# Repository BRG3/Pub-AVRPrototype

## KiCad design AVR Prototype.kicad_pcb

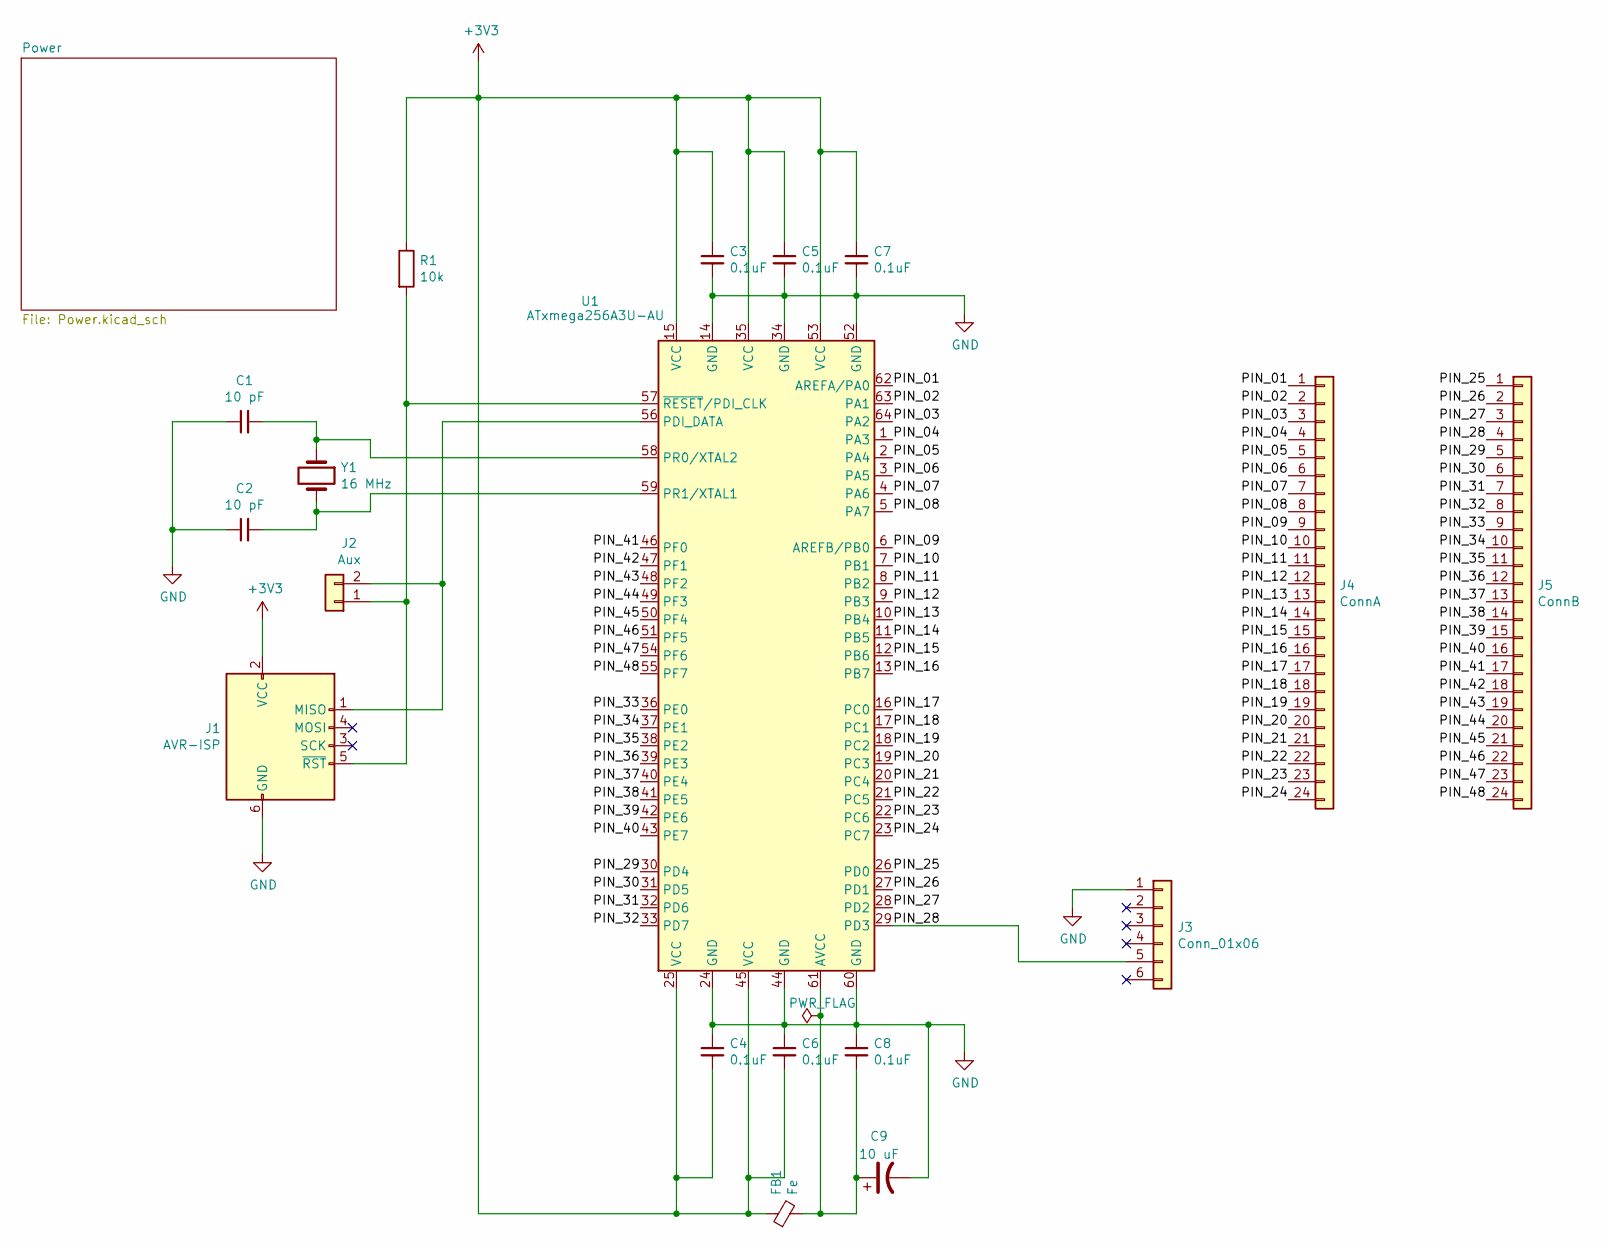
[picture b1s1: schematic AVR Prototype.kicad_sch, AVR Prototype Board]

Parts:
C1, C2: 10 pF; C_0805_2012Metric_Pad1.18x1.45mm_HandSolder; Manufacturer_Part_Number A001; Mouser Part Number 80-C0805C100K5RACAUTO
C3, C4, C5, C6, C7, C8: 0.1uF; C_0805_2012Metric_Pad1.18x1.45mm_HandSolder; Manufacturer_Part_Number A002; Mouser Part Number 80-C0805C104J5RAUTO
C9: 10 uF; C_Radial_D5.0mm_H11.0mm_P2.00mm; Mouser Part Number 667-ECA-2AM100
FB1: Fe; R_0805_2012Metric_Pad1.20x1.40mm_HandSolder; Manufacturer_Part_Number A005; Mouser Part Number 963-BK2125HS101-T
J1: AVR-ISP; AVR_ISP; Manufacturer_Part_Number B105; Mouser Part Number 485-1465
J2: Aux; PinHeader_1x02_P2.54mm_Vertical; Manufacturer_Part_Number B110
J3: Conn_01x06; PinHeader_1x06_P2.54mm_Vertical; Manufacturer_Part_Number B107
J4: ConnA; PinHeader_1x24_P2.54mm_Vertical; Manufacturer_Part_Number B106
J5: ConnB; PinHeader_1x24_P2.54mm_Vertical; Manufacturer_Part_Number B106
R1: 10k; R_0805_2012Metric_Pad1.20x1.40mm_HandSolder; Manufacturer_Part_Number A008; Mouser Part Number 667-ERJ-6GEYJ103V
U1: ATxmega256A3U-AU; TQFP-64_14x14mm_P0.8mm; Manufacturer_Part_Number C201; Mouser Part Number 556-ATXMEGA256A3U-AU
Y1: 16 MHz; Crystal_HC49-U_Vertical; Manufacturer_Part_Number B115; Mouser Part Number 815-ABL-16-B1U

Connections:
+3V3: C3.1, C4.2, C5.1, C6.2, C7.1, FB1.1, J1.2 (VCC), R1.1, U1.15 (VCC), U1.25 (VCC), U1.35 (VCC), U1.45 (VCC), U1.53 (VCC); also elsewhere on the board
/PIN_01: J4.1, U1.62 (AREFA/PA0)
/PIN_02: J4.2, U1.63 (PA1)
/PIN_03: J4.3, U1.64 (PA2)
/PIN_04: J4.4, U1.1 (PA3)
/PIN_05: J4.5, U1.2 (PA4)
/PIN_06: J4.6, U1.3 (PA5)
/PIN_07: J4.7, U1.4 (PA6)
/PIN_08: J4.8, U1.5 (PA7)
/PIN_09: J4.9, U1.6 (AREFB/PB0)
/PIN_10: J4.10, U1.7 (PB1)
/PIN_11: J4.11, U1.8 (PB2)
/PIN_12: J4.12, U1.9 (PB3)
/PIN_13: J4.13, U1.10 (PB4)
/PIN_14: J4.14, U1.11 (PB5)
/PIN_15: J4.15, U1.12 (PB6)
/PIN_16: J4.16, U1.13 (PB7)
/PIN_17: J4.17, U1.16 (PC0)
/PIN_18: J4.18, U1.17 (PC1)
/PIN_19: J4.19, U1.18 (PC2)
/PIN_20: J4.20, U1.19 (PC3)
/PIN_21: J4.21, U1.20 (PC4)
/PIN_22: J4.22, U1.21 (PC5)
/PIN_23: J4.23, U1.22 (PC6)
/PIN_24: J4.24, U1.23 (PC7)
/PIN_25: J5.1, U1.26 (PD0)
/PIN_26: J5.2, U1.27 (PD1)
/PIN_27: J5.3, U1.28 (PD2)
/PIN_28: J3.5, J5.4, U1.29 (PD3)
/PIN_29: J5.5, U1.30 (PD4)
/PIN_30: J5.6, U1.31 (PD5)
/PIN_31: J5.7, U1.32 (PD6)
/PIN_32: J5.8, U1.33 (PD7)
/PIN_33: J5.9, U1.36 (PE0)
/PIN_34: J5.10, U1.37 (PE1)
/PIN_35: J5.11, U1.38 (PE2)
/PIN_36: J5.12, U1.39 (PE3)
/PIN_37: J5.13, U1.40 (PE4)
/PIN_38: J5.14, U1.41 (PE5)
/PIN_39: J5.15, U1.42 (PE6)
/PIN_40: J5.16, U1.43 (PE7)
/PIN_41: J5.17, U1.46 (PF0)
/PIN_42: J5.18, U1.47 (PF1)
/PIN_43: J5.19, U1.48 (PF2)
/PIN_44: J5.20, U1.49 (PF3)
/PIN_45: J5.21, U1.50 (PF4)
/PIN_46: J5.22, U1.51 (PF5)
/PIN_47: J5.23, U1.54 (PF6)
/PIN_48: J5.24, U1.55 (PF7)
GND: C1.1, C2.1, C3.2, C4.1, C5.2, C6.1, C7.2, C8.1, C9.2, J1.6 (GND), J3.1, U1.14 (GND), U1.24 (GND), U1.34 (GND), U1.44 (GND), U1.52 (GND), U1.60 (GND); also elsewhere on the board
unnamed: J1.1 (MISO), J2.2, U1.56 (PDI_DATA)
unnamed: J1.5 (~RST), J2.1, R1.2, U1.57 (~RESET/PDI_CLK)
unnamed: C8.2, C9.1, FB1.2, U1.61 (AVCC)
unnamed: C1.2, U1.58 (PR0/XTAL2), Y1.1
unnamed: C2.2, U1.59 (PR1/XTAL1), Y1.2

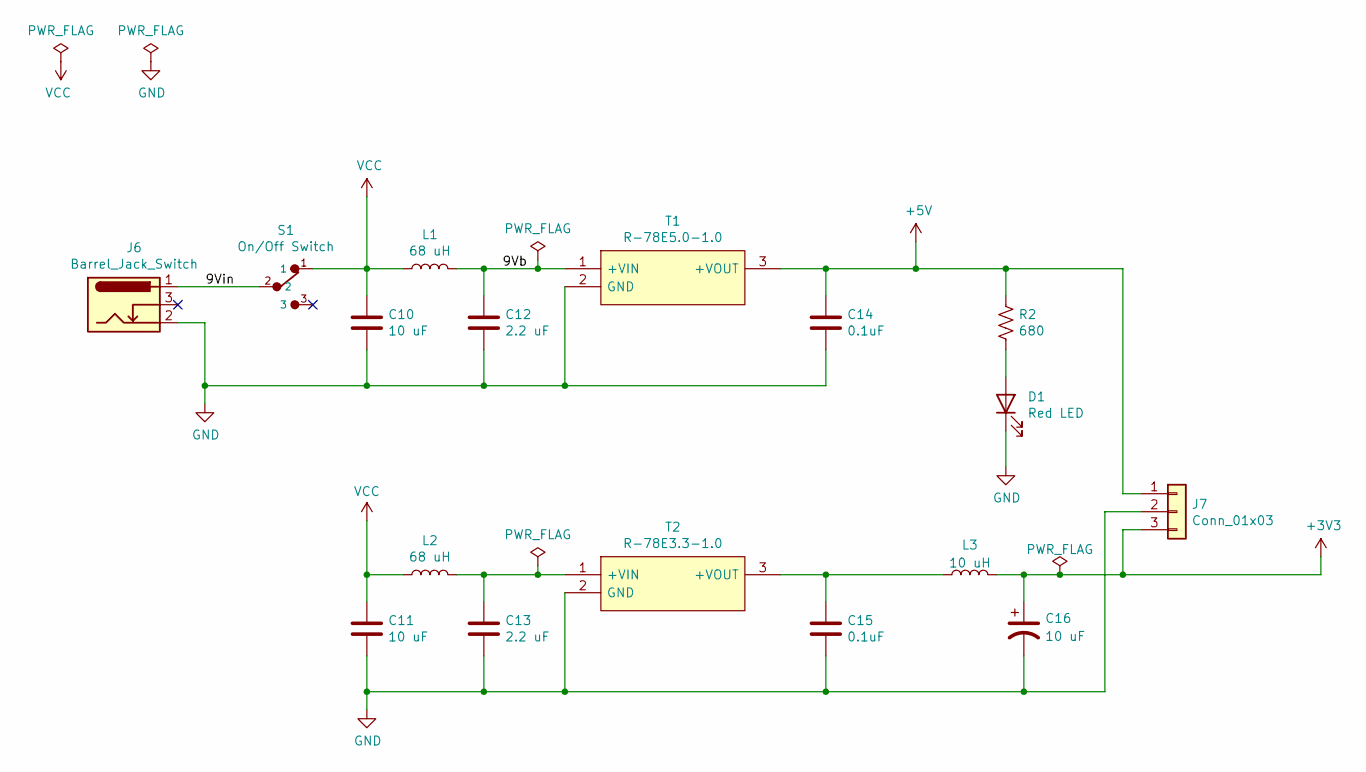
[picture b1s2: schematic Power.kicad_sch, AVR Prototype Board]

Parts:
C10, C11: 10 uF; C_2220_5750Metric_Pad1.97x5.40mm_HandSolder; Manufacturer_Part_Number A004; Mouser Part Number 810-CGA9N3X7S2A106KS
C12, C13: 2.2 uF; C_0805_2012Metric_Pad1.18x1.45mm_HandSolder; Manufacturer_Part_Number A003; Mouser Part Number 81-GRM21BD72A225KE01L
C14, C15: 0.1uF; C_0805_2012Metric_Pad1.18x1.45mm_HandSolder; Manufacturer_Part_Number A002; Mouser Part Number 80-C0805C104J5RAUTO
C16: 10 uF; C_Radial_D5.0mm_H11.0mm_P2.00mm; Mouser Part Number 667-ECA-2AM100
D1: Red LED; LED_D3.0mm; Manufacturer_Part_Number B103; Mouser Part Number 78-TLHK46Q1R2
J6: Barrel_Jack_Switch; PJ-102AH; Manufacturer_Part_Number B108; Mouser Part Number 490-PJ-102AH
J7: Conn_01x03; PinHeader_1x03_P2.54mm_Vertical; Manufacturer_Part_Number B109
L1, L2: 68 uH; L_Taiyo-Yuden_NR-60xx_HandSoldering; Manufacturer_Part_Number A006; Mouser Part Number 963-NRS6012T680MMGJ
L3: 10 uH; SBT0210; Mouser Part Number 80-SBT-0210
R2: 680; R_0805_2012Metric_Pad1.20x1.40mm_HandSolder; Manufacturer_Part_Number A007; Mouser Part Number 603-RC0805FR-13680RL
S1: On/Off Switch; SW_1101M2S3CQE2; Mouser Part Number 611-1101M2S3CQE2
T1: R-78E5.0-1.0; Manufacturer_Part_Number R-78E5.0-1.0; Mouser Part Number 919-R-78E5.0-1.0
T2: R-78E3.3-1.0; Manufacturer_Part_Number R-78E3.3-1.0; Mouser Part Number 919-R-78E3.3-1.0

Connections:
+3V3: C16.1, J7.3, L3.2; also elsewhere on the board
+5V: C14.1, J7.1, R2.1, T1.3 (+VOUT)
/Power/9Vb: C12.1, L1.2, T1.1 (+VIN)
/Power/9Vin: J6.1, S1.2
GND: C10.2, C11.2, C12.2, C13.2, C14.2, C15.2, C16.2, D1.1 (K), J6.2, J7.2, T1.2 (GND), T2.2 (GND); also elsewhere on the board
unnamed: D1.2 (A), R2.2
unnamed: C13.1, L2.2, T2.1 (+VIN)
unnamed: C15.1, L3.1, T2.3 (+VOUT)
VCC: C10.1, C11.1, L1.1, L2.1, S1.1

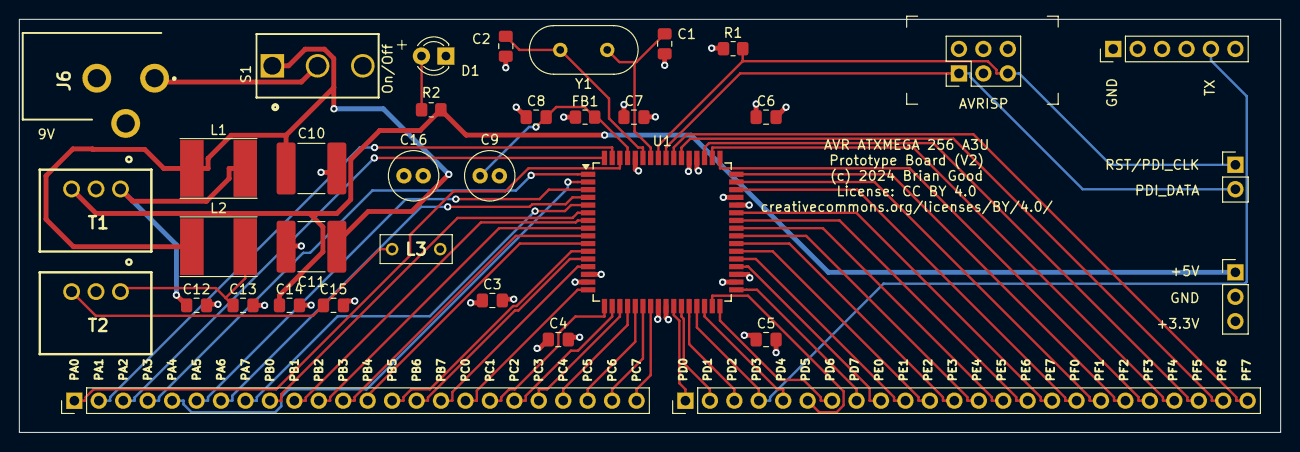
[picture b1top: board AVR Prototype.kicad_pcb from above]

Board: 4 copper layers, 131.1 x 42.9 mm, 35 parts (0 on the bottom side), 62 nets.

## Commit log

2023-02-06 Original V2 Update
2023-02-07 Routed by FreeRouting
2023-02-21 Removed fp-info-cache from tracking
2023-02-21 Removed generated files
2023-02-21 More cleanup of generated
2024-08-29 Updated V3.3 Converter to VCC input

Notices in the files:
AVR Prototype.kicad_pcb:
(c) 2024 Brian Good
License: CC BY 4.0
creativecommons.org/licenses/BY/4.0
AVR Prototype.kicad_sch:
Brian Good - Copyright 2022
